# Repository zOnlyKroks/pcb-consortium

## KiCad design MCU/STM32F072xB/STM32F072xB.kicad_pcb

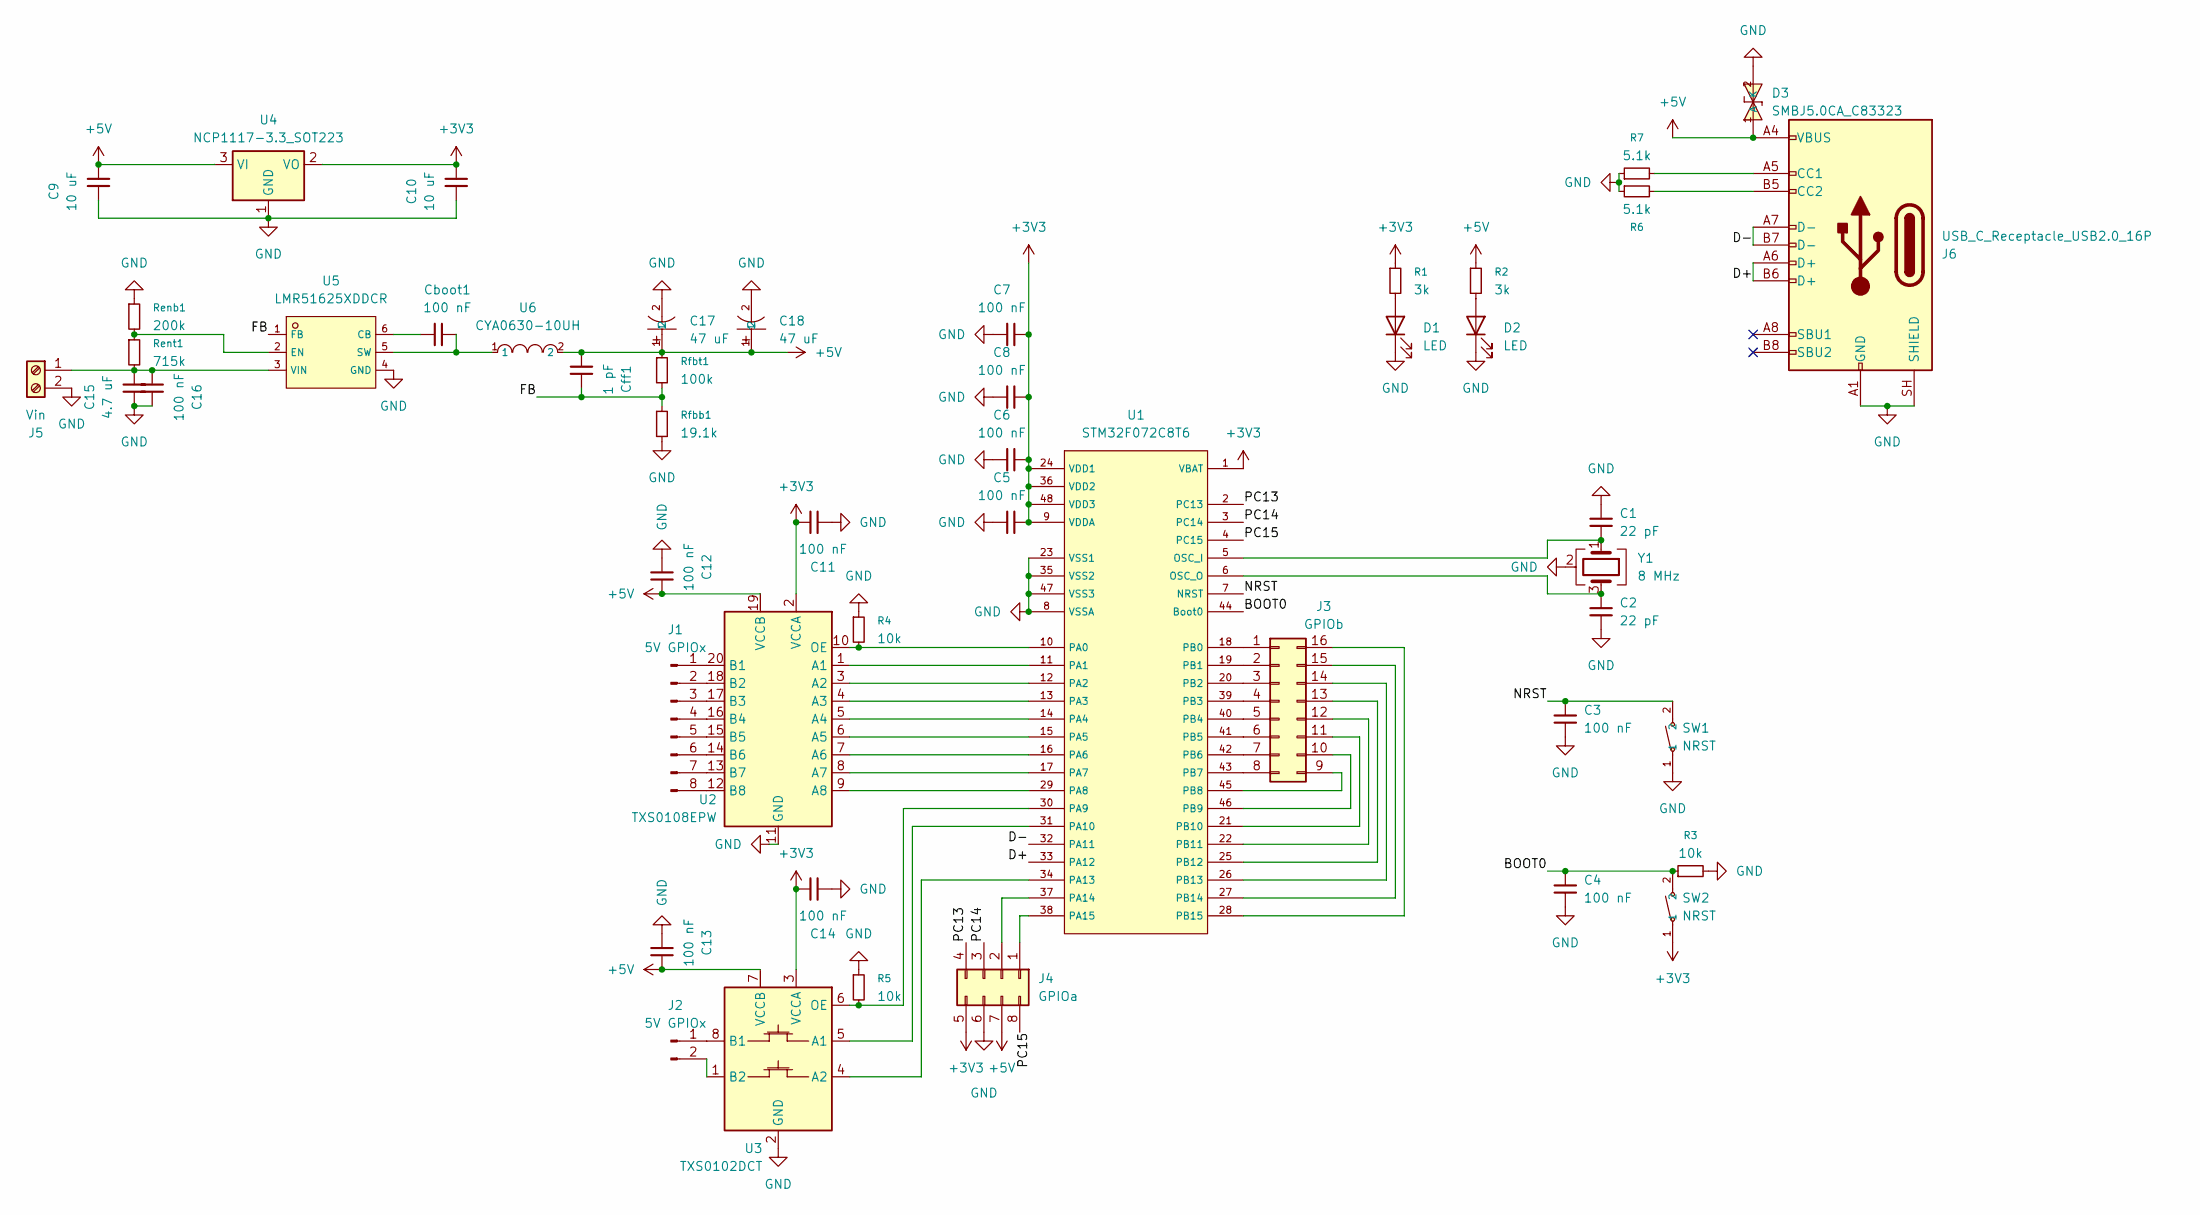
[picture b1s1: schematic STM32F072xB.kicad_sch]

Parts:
C1, C2: 22 pF; C_0603_1608Metric
C3, C4, C5, C6, C7, C8, C11, C12, C13, C14: 100 nF; C_0603_1608Metric
C9, C10: 10 uF; C_0805_2012Metric
C15: 4.7 uF; C_0805_2012Metric
C16: 100 nF; C_0805_2012Metric
C17, C18: 47 uF; C141425_CAP-SMD_BD6_3-L6_6-W6_6-FD; LCSC C141425
Cboot1: 100 nF; C_0805_2012Metric
Cff1: 1 pF; C_0805_2012Metric
D1, D2: LED; LED_0805_2012Metric
D3: SMBJ5.0CA_C83323; C83323_SMB_L4_6-W3_6-LS5_3-BI; LCSC C83323
J1: 5V GPIOx; PinHeader_1x08_P2.54mm_Vertical
J2: 5V GPIOx; PinHeader_1x02_P2.54mm_Vertical
J3: GPIOb; PinHeader_2x08_P2.54mm_Vertical
J4: GPIOa; PinHeader_2x04_P2.54mm_Vertical
J5: Vin; WJ500V-5.08-2P
J6: USB_C_Receptacle_USB2.0_16P; USB_C_Receptacle_HRO_TYPE-C-31-M-12
R1, R2: 3k; R_0603_1608Metric
R3, R4, R5: 10k; R_0603_1608Metric
R6, R7: 5.1k; R_0603_1608Metric
Renb1: 200k; R_0603_1608Metric
Rent1: 715k; R_0603_1608Metric
Rfbb1: 19.1k; R_0603_1608Metric
Rfbt1: 100k; R_0603_1608Metric
SW1, SW2: NRST; C53447012_SW-SMD_L3_9-W3_0-LS5_0; LCSC C53447012
U1: STM32F072C8T6; C80488_LQFP-48_L7_0-W7_0-P0_50-LS9_0-BL; LCSC C80488
U2: TXS0108EPW; TSSOP-20_4.4x6.5mm_P0.65mm
U3: TXS0102DCT; SSOP-8_2.95x2.8mm_P0.65mm
U4: NCP1117-3.3_SOT223; SOT-223-3_TabPin2
U5: LMR51625XDDCR; C44750835_SOT-23-6_L2_9-W1_6-P0_95-LS2_9-BL; LCSC C44750835
U6: CYA0630-10UH; C5189958_IND-SMD_L7_2-W6_6_GPSR07X0; LCSC C5189958
Y1: 8 MHz; Crystal_SMD_3225-4Pin_3.2x2.5mm

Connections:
+3V3: C5.1, C6.1, C7.1, C8.1, C10.1, C11.1, C14.1, J4.5, R1.1, SW2.1, U1.1 (VBAT), U1.9 (VDDA), U1.24 (VDD1), U1.36 (VDD2), U1.48 (VDD3), U2.2 (VCCA), U3.3 (VCCA), U4.2 (VO)
+5V: C9.1, C12.1, C13.1, C17.1, C18.1, Cff1.1, D3.1 (K), J4.7, J6.A4 (VBUS), J6.A9 (VBUS), J6.B4 (VBUS), J6.B9 (VBUS), R2.1, Rfbt1.1, U2.19 (VCCB), U3.7 (VCCB), U4.3 (VI), U6.2
/BOOT0: C4.2, R3.1, SW2.2, U1.44 (Boot0)
/D+: J6.A6 (D+), J6.B6 (D+), U1.33 (PA12)
/D-: J6.A7 (D-), J6.B7 (D-), U1.32 (PA11)
/FB: Cff1.2, Rfbb1.1, Rfbt1.2, U5.1 (FB)
/NRST: C3.2, SW1.2, U1.7 (NRST)
/PC13: J4.4, U1.2 (PC13)
/PC14: J4.3, U1.3 (PC14)
/PC15: J4.8, U1.4 (PC15)
GND: C1.2, C2.1, C3.1, C4.1, C5.2, C6.2, C7.2, C8.2, C9.2, C10.2, C11.2, C12.2, C13.2, C14.2, C15.2, C16.2, C17.2, C18.2, D1.1 (K), D2.1 (K), D3.2 (A), J4.6, J5.2, J6.A1 (GND), J6.A12 (GND), J6.B1 (GND), J6.B12 (GND), J6.SH (SHIELD), R3.2, R4.1, R5.1, R6.1, R7.1, Renb1.1, Rfbb1.2, SW1.1, U1.8 (VSSA), U1.23 (VSS1), U1.35 (VSS2), U1.47 (VSS3), U2.11 (GND), U3.2 (GND), U4.1 (GND), U5.4 (GND), Y1.2 (G), Y1.4 (G)
unnamed: D1.2 (A), R1.2
unnamed: D2.2 (A), R2.2
unnamed: J1.1, U2.20 (B1)
unnamed: J1.2, U2.18 (B2)
unnamed: J1.3, U2.17 (B3)
unnamed: J1.4, U2.16 (B4)
unnamed: J1.5, U2.15 (B5)
unnamed: J1.6, U2.14 (B6)
unnamed: J1.7, U2.13 (B7)
unnamed: J1.8, U2.12 (B8)
unnamed: J2.1, U3.8 (B1)
unnamed: J2.2, U3.1 (B2)
unnamed: J3.1, U1.18 (PB0)
unnamed: J3.2, U1.19 (PB1)
unnamed: J3.3, U1.20 (PB2)
unnamed: J3.4, U1.39 (PB3)
unnamed: J3.5, U1.40 (PB4)
unnamed: J3.6, U1.41 (PB5)
unnamed: J3.7, U1.42 (PB6)
unnamed: J3.8, U1.43 (PB7)
unnamed: J3.9, U1.45 (PB8)
unnamed: J3.10, U1.46 (PB9)
unnamed: J3.11, U1.21 (PB10)
unnamed: J3.12, U1.22 (PB11)
unnamed: J3.13, U1.25 (PB12)
unnamed: J3.14, U1.26 (PB13)
unnamed: J3.15, U1.27 (PB14)
unnamed: J3.16, U1.28 (PB15)
unnamed: J4.1, U1.38 (PA15)
unnamed: J4.2, U1.37 (PA14)
unnamed: C15.1, C16.1, J5.1, Rent1.2, U5.3 (VIN)
unnamed: J6.A5 (CC1), R7.2
unnamed: J6.B5 (CC2), R6.2
unnamed: C1.1, U1.5 (OSC_I), Y1.1
unnamed: C2.2, U1.6 (OSC_O), Y1.3
unnamed: R4.2, U1.10 (PA0), U2.10 (OE)
unnamed: U1.11 (PA1), U2.1 (A1)
unnamed: U1.12 (PA2), U2.3 (A2)
unnamed: U1.13 (PA3), U2.4 (A3)
unnamed: U1.14 (PA4), U2.5 (A4)
unnamed: U1.15 (PA5), U2.6 (A5)
unnamed: U1.16 (PA6), U2.7 (A6)
unnamed: U1.17 (PA7), U2.8 (A7)
unnamed: U1.29 (PA8), U2.9 (A8)
unnamed: R5.2, U1.30 (PA9), U3.6 (OE)
unnamed: U1.31 (PA10), U3.5 (A1)
unnamed: U1.34 (PA13), U3.4 (A2)
unnamed: Cboot1.1, U5.6 (CB)
unnamed: Renb1.2, Rent1.1, U5.2 (EN)
unnamed: Cboot1.2, U5.5 (SW), U6.1

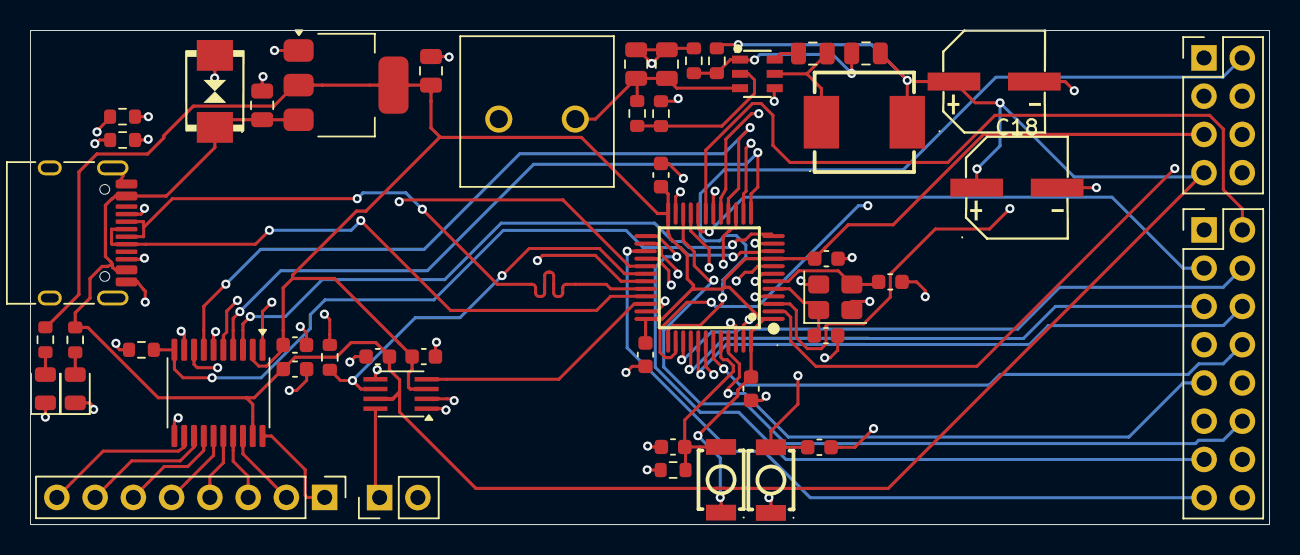
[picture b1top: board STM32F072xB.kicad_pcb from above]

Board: 4 copper layers, 82.3 x 32.8 mm, 49 parts (0 on the bottom side), 61 nets.

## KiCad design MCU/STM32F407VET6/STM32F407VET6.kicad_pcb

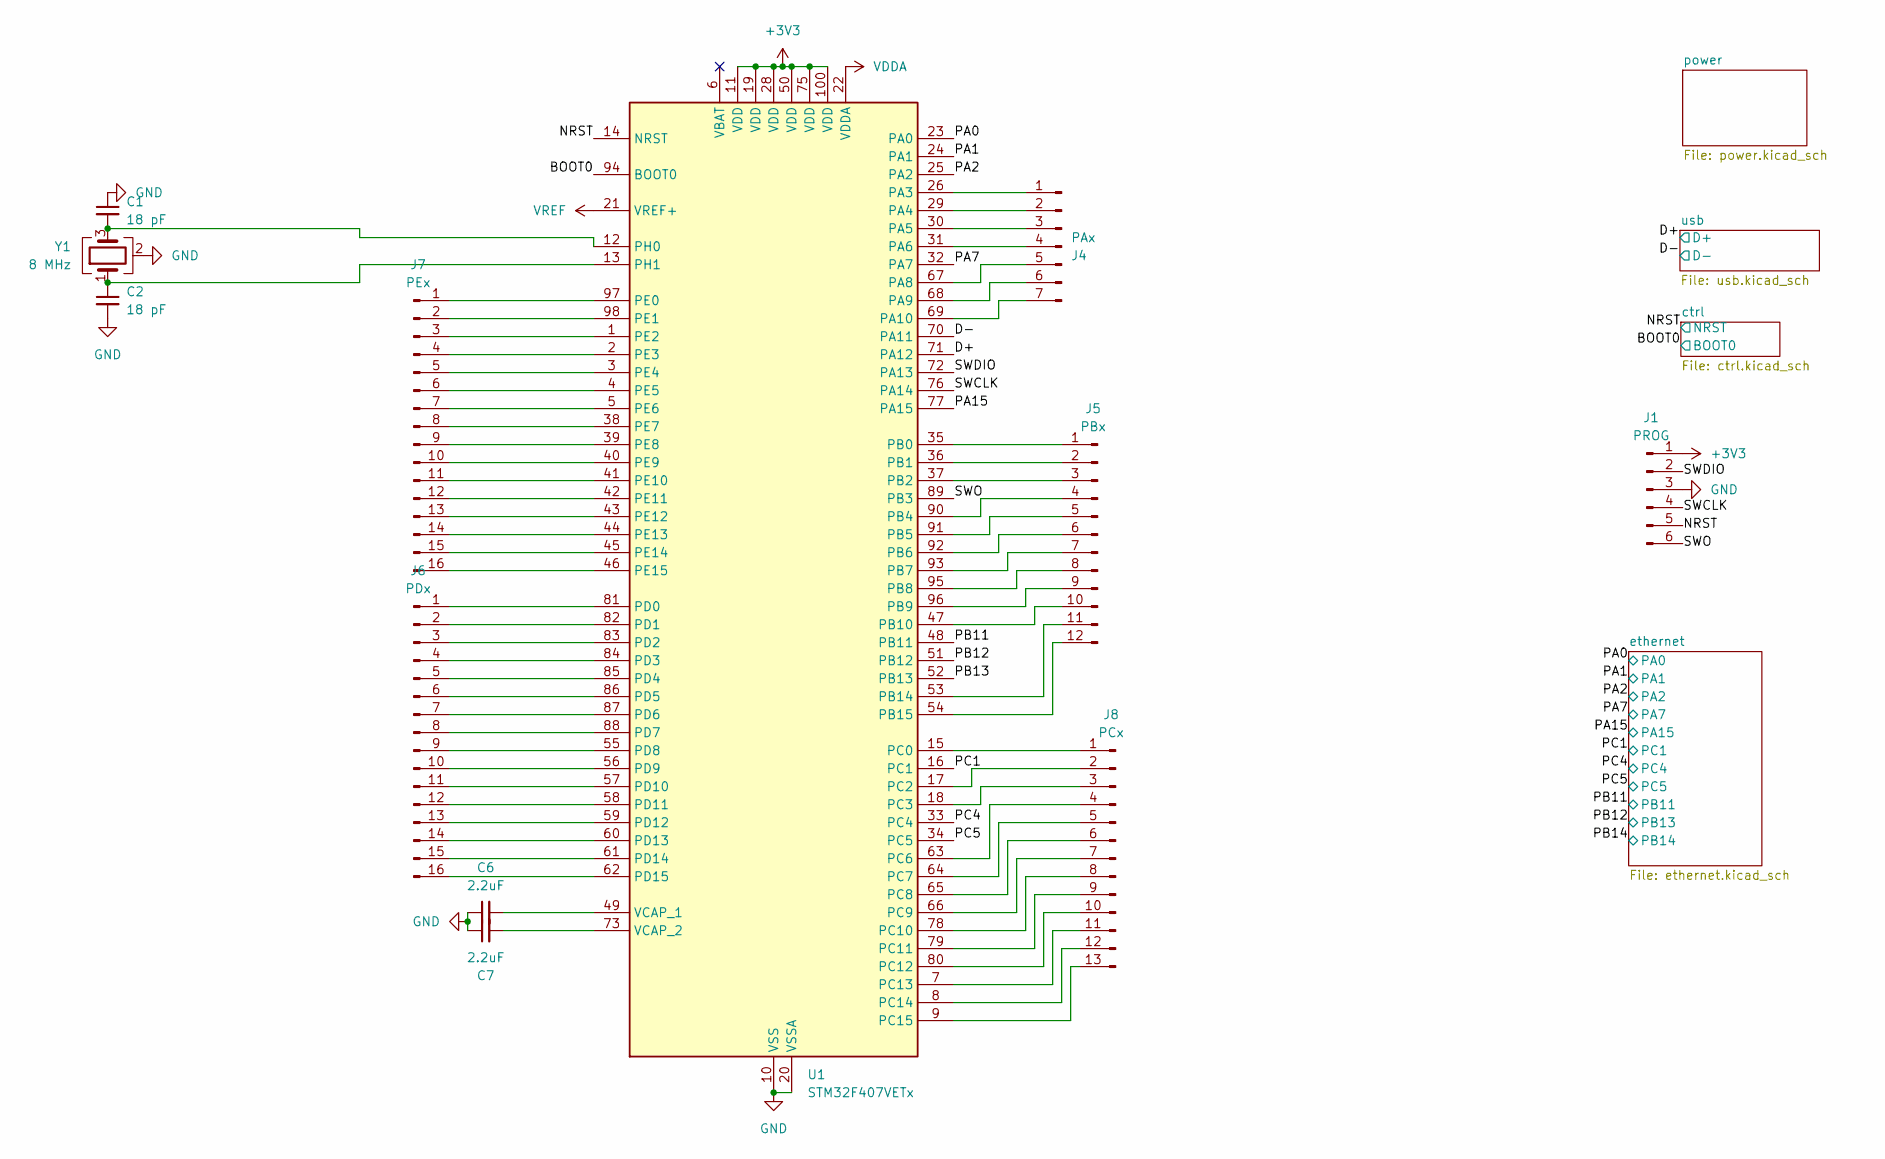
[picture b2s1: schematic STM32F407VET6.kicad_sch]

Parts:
C1, C2: 18 pF; C_0603_1608Metric
C6, C7: 2.2uF; C_0603_1608Metric
J1: PROG; PinHeader_1x06_P2.54mm_Vertical
J4: PAx; PinHeader_1x07_P2.54mm_Vertical
J5: PBx; PinHeader_1x12_P2.54mm_Vertical
J6: PDx; PinHeader_1x16_P2.54mm_Vertical
J7: PEx; PinHeader_1x16_P2.54mm_Vertical
J8: PCx; PinHeader_1x13_P2.54mm_Vertical
U1: STM32F407VETx; LQFP-100_14x14mm_P0.5mm
Y1: 8 MHz; Crystal_SMD_3225-4Pin_3.2x2.5mm

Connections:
+3V3: J1.1, U1.11 (VDD), U1.19 (VDD), U1.28 (VDD), U1.50 (VDD), U1.75 (VDD), U1.100 (VDD); also elsewhere on the board
/BOOT0: U1.94 (BOOT0); also elsewhere on the board
/D+: U1.71 (PA12); also elsewhere on the board
/D-: U1.70 (PA11); also elsewhere on the board
/NRST: J1.5, U1.14 (NRST); also elsewhere on the board
/PA0: U1.23 (PA0); also elsewhere on the board
/PA1: U1.24 (PA1); also elsewhere on the board
/PA2: U1.25 (PA2); also elsewhere on the board
/PA7: U1.32 (PA7); also elsewhere on the board
/PA15: U1.77 (PA15); also elsewhere on the board
/PB11: U1.48 (PB11); also elsewhere on the board
/PB12: U1.51 (PB12); also elsewhere on the board
/PB13: U1.52 (PB13)
/PC1: U1.16 (PC1); also elsewhere on the board
/PC4: U1.33 (PC4); also elsewhere on the board
/PC5: U1.34 (PC5); also elsewhere on the board
/SWCLK: J1.4, U1.76 (PA14)
/SWDIO: J1.2, U1.72 (PA13)
/SWO: J1.6, U1.89 (PB3)
GND: C1.1, C2.2, C6.1, C7.1, J1.3, U1.10 (VSS), U1.20 (VSSA), U1.27 (VSS), U1.74 (VSS), U1.99 (VSS), Y1.2 (G), Y1.4 (G); also elsewhere on the board
unnamed: J4.1, U1.26 (PA3)
unnamed: J4.2, U1.29 (PA4)
unnamed: J4.3, U1.30 (PA5)
unnamed: J4.4, U1.31 (PA6)
unnamed: J4.5, U1.67 (PA8)
unnamed: J4.6, U1.68 (PA9)
unnamed: J4.7, U1.69 (PA10)
unnamed: J5.1, U1.35 (PB0)
unnamed: J5.2, U1.36 (PB1)
unnamed: J5.3, U1.37 (PB2)
unnamed: J5.4, U1.90 (PB4)
unnamed: J5.5, U1.91 (PB5)
unnamed: J5.6, U1.92 (PB6)
unnamed: J5.7, U1.93 (PB7)
unnamed: J5.8, U1.95 (PB8)
unnamed: J5.9, U1.96 (PB9)
unnamed: J5.10, U1.47 (PB10)
unnamed: J5.11, U1.53 (PB14)
unnamed: J5.12, U1.54 (PB15)
unnamed: J6.1, U1.81 (PD0)
unnamed: J6.2, U1.82 (PD1)
unnamed: J6.3, U1.83 (PD2)
unnamed: J6.4, U1.84 (PD3)
unnamed: J6.5, U1.85 (PD4)
unnamed: J6.6, U1.86 (PD5)
unnamed: J6.7, U1.87 (PD6)
unnamed: J6.8, U1.88 (PD7)
unnamed: J6.9, U1.55 (PD8)
unnamed: J6.10, U1.56 (PD9)
unnamed: J6.11, U1.57 (PD10)
unnamed: J6.12, U1.58 (PD11)
unnamed: J6.13, U1.59 (PD12)
unnamed: J6.14, U1.60 (PD13)
unnamed: J6.15, U1.61 (PD14)
unnamed: J6.16, U1.62 (PD15)
unnamed: J7.1, U1.97 (PE0)
unnamed: J7.2, U1.98 (PE1)
unnamed: J7.3, U1.1 (PE2)
unnamed: J7.4, U1.2 (PE3)
unnamed: J7.5, U1.3 (PE4)
unnamed: J7.6, U1.4 (PE5)
unnamed: J7.7, U1.5 (PE6)
unnamed: J7.8, U1.38 (PE7)
unnamed: J7.9, U1.39 (PE8)
unnamed: J7.10, U1.40 (PE9)
unnamed: J7.11, U1.41 (PE10)
unnamed: J7.12, U1.42 (PE11)
unnamed: J7.13, U1.43 (PE12)
unnamed: J7.14, U1.44 (PE13)
unnamed: J7.15, U1.45 (PE14)
unnamed: J7.16, U1.46 (PE15)
unnamed: J8.1, U1.15 (PC0)
unnamed: J8.2, U1.17 (PC2)
unnamed: J8.3, U1.18 (PC3)
unnamed: J8.4, U1.63 (PC6)
unnamed: J8.5, U1.64 (PC7)
unnamed: J8.6, U1.65 (PC8)
unnamed: J8.7, U1.66 (PC9)
unnamed: J8.8, U1.78 (PC10)
unnamed: J8.9, U1.79 (PC11)
unnamed: J8.10, U1.80 (PC12)
unnamed: J8.11, U1.7 (PC13)
unnamed: J8.12, U1.8 (PC14)
unnamed: J8.13, U1.9 (PC15)
unnamed: C1.2, U1.12 (PH0), Y1.3
unnamed: C2.1, U1.13 (PH1), Y1.1
unnamed: C6.2, U1.49 (VCAP_1)
unnamed: C7.2, U1.73 (VCAP_2)
VDDA: U1.22 (VDDA); also elsewhere on the board
VREF: U1.21 (VREF+); also elsewhere on the board

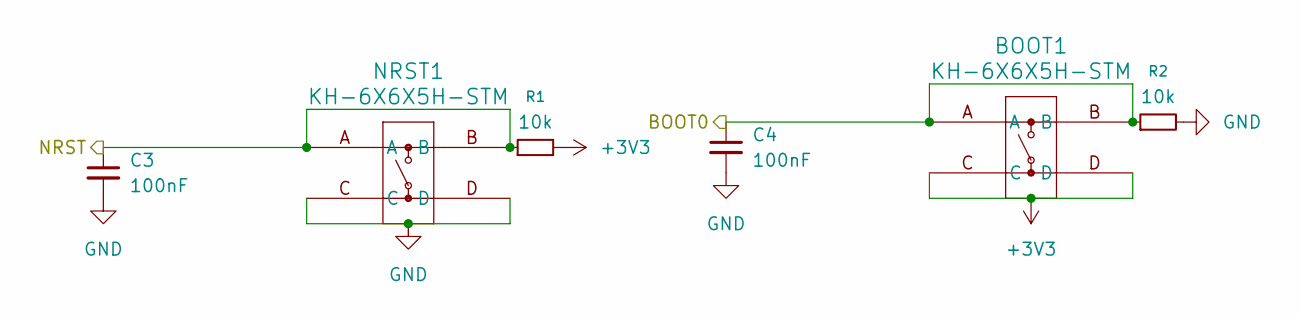
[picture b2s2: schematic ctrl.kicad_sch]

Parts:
BOOT1: KH-6X6X5H-STM; KH-6X6X5H-STM_SKE
C3, C4: 100nF; C_0603_1608Metric
NRST1: KH-6X6X5H-STM; KH-6X6X5H-STM_SKE
R1, R2: 10k; R_0603_1608Metric

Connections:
+3V3: BOOT1.C, BOOT1.D, R1.2; also elsewhere on the board
/BOOT0: BOOT1.A, BOOT1.B, C4.1, R2.1; also elsewhere on the board
/NRST: C3.1, NRST1.A, NRST1.B, R1.1; also elsewhere on the board
GND: C3.2, C4.2, NRST1.C, NRST1.D, R2.2; also elsewhere on the board

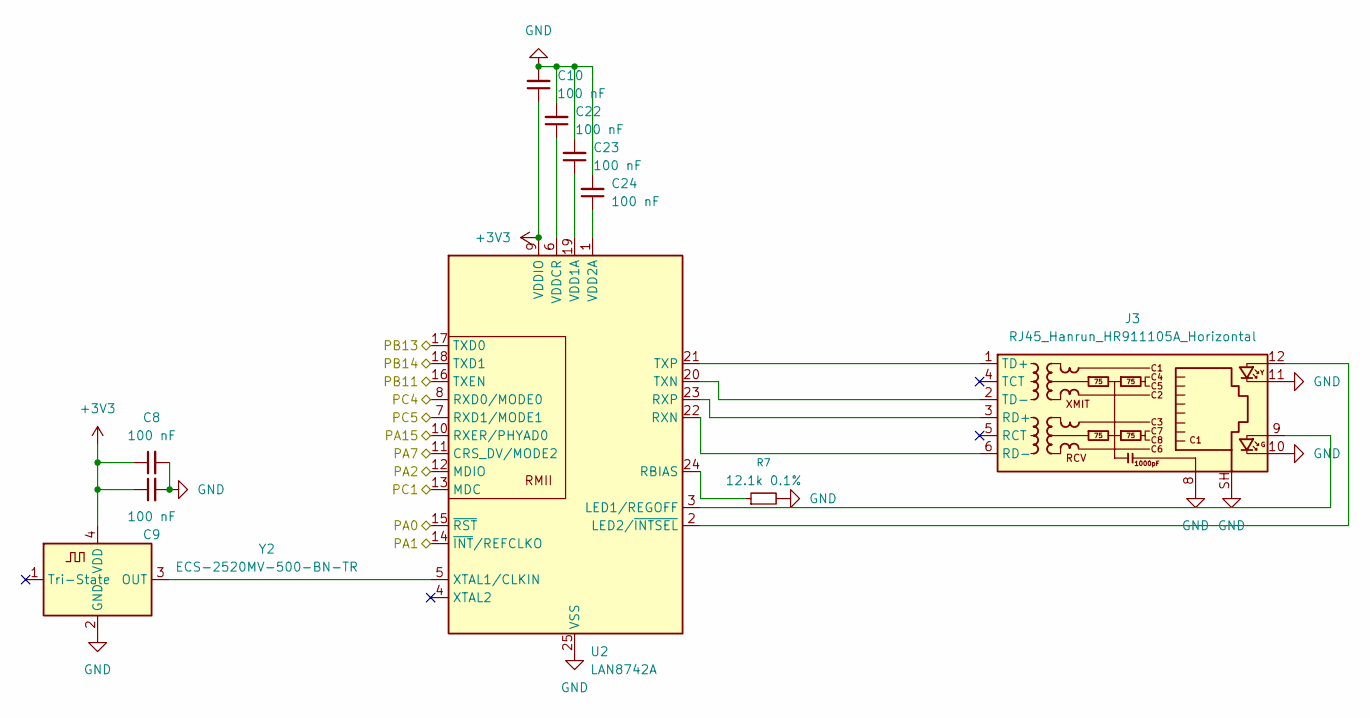
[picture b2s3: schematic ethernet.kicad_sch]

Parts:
C8, C9, C10, C22, C23, C24: 100 nF; C_0603_1608Metric
J3: RJ45_Hanrun_HR911105A_Horizontal
R7: 12.1k 0.1%; R_0603_1608Metric
U2: LAN8742A; VQFN-24-1EP_4x4mm_P0.5mm_EP2.5x2.5mm_ThermalVias
Y2: ECS-2520MV-500-BN-TR; Oscillator_SMD_ECS_2520MV-xxx-xx-4Pin_2.5x2.0mm

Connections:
+3V3: C8.1, C9.1, C10.1, U2.9 (VDDIO), Y2.4 (VDD); also elsewhere on the board
/PA0: U2.15 (~RST); also elsewhere on the board
/PA1: U2.14 (~INT/REFCLKO); also elsewhere on the board
/PA2: U2.12 (MDIO); also elsewhere on the board
/PA7: U2.11 (CRS_DV/MODE2); also elsewhere on the board
/PA15: U2.10 (RXER/PHYAD0); also elsewhere on the board
/PB11: U2.16 (TXEN); also elsewhere on the board
/PB12: U2.17 (TXD0); also elsewhere on the board
/PB14: U2.18 (TXD1)
/PC1: U2.13 (MDC); also elsewhere on the board
/PC4: U2.8 (RXD0/MODE0); also elsewhere on the board
/PC5: U2.7 (RXD1/MODE1); also elsewhere on the board
GND: C8.2, C9.2, C10.2, C22.2, C23.2, C24.2, J3.8, J3.10, J3.11, J3.SH, R7.2, U2.25 (VSS), Y2.2 (GND); also elsewhere on the board
unnamed: J3.3 (RD+), U2.23 (RXP)
unnamed: J3.6 (RD-), U2.22 (RXN)
unnamed: J3.1 (TD+), U2.21 (TXP)
unnamed: J3.2 (TD-), U2.20 (TXN)
unnamed: J3.9, U2.3 (LED1/REGOFF)
unnamed: J3.12, U2.2 (LED2/~INTSEL)
unnamed: R7.1, U2.24 (RBIAS)
unnamed: C23.1, U2.19 (VDD1A)
unnamed: C24.1, U2.1 (VDD2A)
unnamed: C22.1, U2.6 (VDDCR)
unnamed: U2.5 (XTAL1/CLKIN), Y2.3 (OUT)

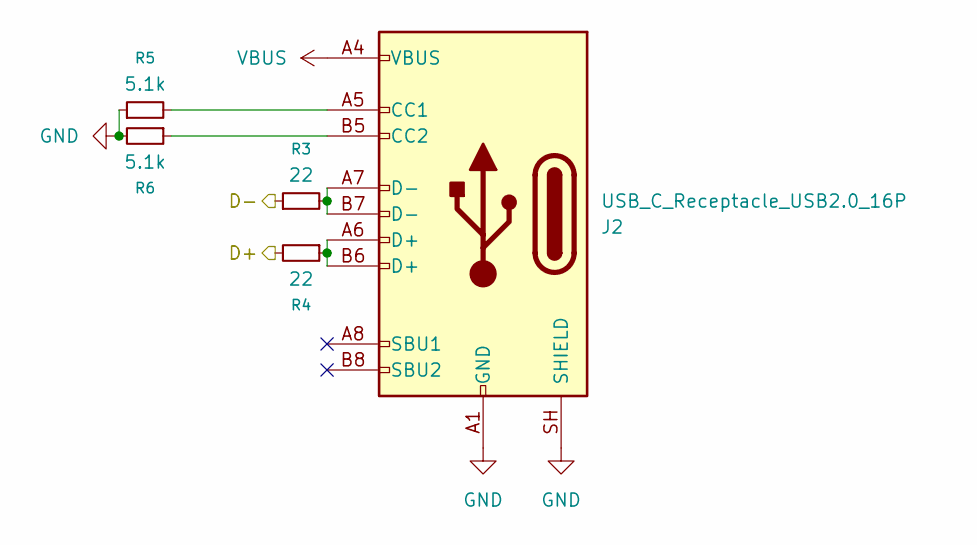
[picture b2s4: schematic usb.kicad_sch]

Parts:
J2: USB_C_Receptacle_USB2.0_16P; USB_C_Receptacle_HRO_TYPE-C-31-M-12
R3, R4: 22; R_0603_1608Metric
R5, R6: 5.1k; R_0603_1608Metric

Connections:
/D+: R4.2; also elsewhere on the board
/D-: R3.1; also elsewhere on the board
GND: J2.A1 (GND), J2.A12 (GND), J2.B1 (GND), J2.B12 (GND), J2.SH (SHIELD), R5.1, R6.2; also elsewhere on the board
unnamed: J2.A5 (CC1), R5.2
unnamed: J2.B5 (CC2), R6.1
unnamed: J2.A6 (D+), J2.B6 (D+), R4.1
unnamed: J2.A7 (D-), J2.B7 (D-), R3.2
VBUS: J2.A4 (VBUS), J2.A9 (VBUS), J2.B4 (VBUS), J2.B9 (VBUS); also elsewhere on the board

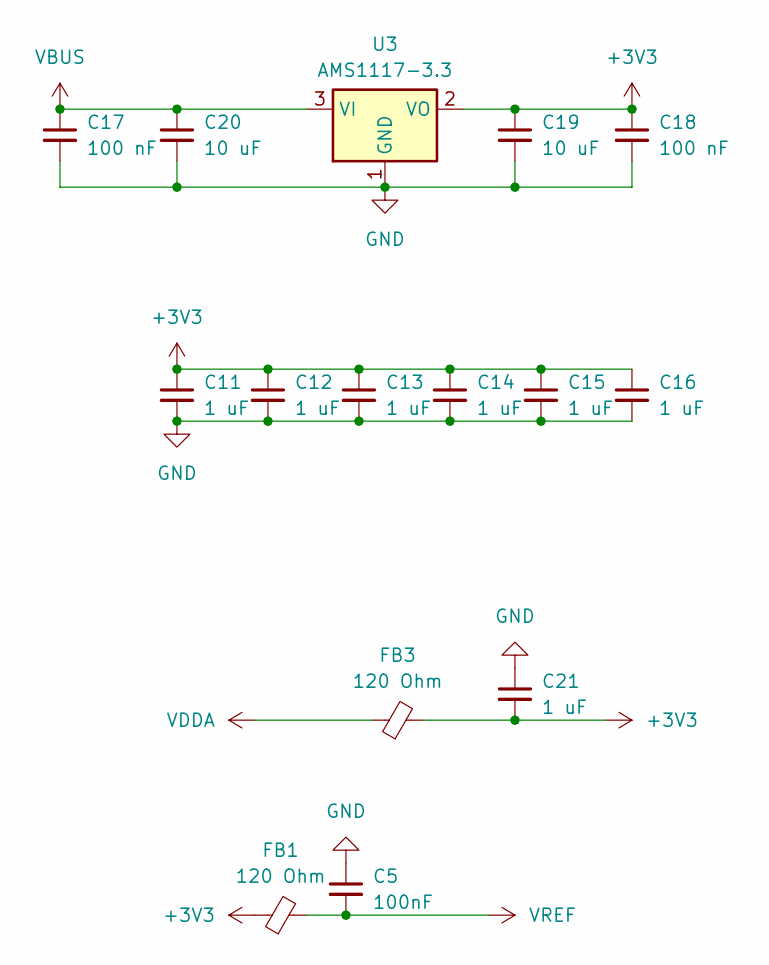
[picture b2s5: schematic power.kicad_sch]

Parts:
C5: 100nF; C_0603_1608Metric
C11, C12, C13, C14, C15, C16, C21: 1 uF; C_0603_1608Metric
C17, C18: 100 nF; C_0603_1608Metric
C19, C20: 10 uF; C_0603_1608Metric
FB1, FB3: 120 Ohm; R_0603_1608Metric
U3: AMS1117-3.3; SOT-223-3_TabPin2

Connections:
+3V3: C11.1, C12.1, C13.1, C14.1, C15.1, C16.1, C18.1, C19.1, C21.2, FB1.1, FB3.2, U3.2 (VO); also elsewhere on the board
GND: C5.1, C11.2, C12.2, C13.2, C14.2, C15.2, C16.2, C17.2, C18.2, C19.2, C20.2, C21.1, U3.1 (GND); also elsewhere on the board
VBUS: C17.1, C20.1, U3.3 (VI); also elsewhere on the board
VDDA: FB3.1; also elsewhere on the board
VREF: C5.2, FB1.2; also elsewhere on the board

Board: 4 copper layers, 48 parts (0 on the bottom side), 105 nets, no tracks yet.

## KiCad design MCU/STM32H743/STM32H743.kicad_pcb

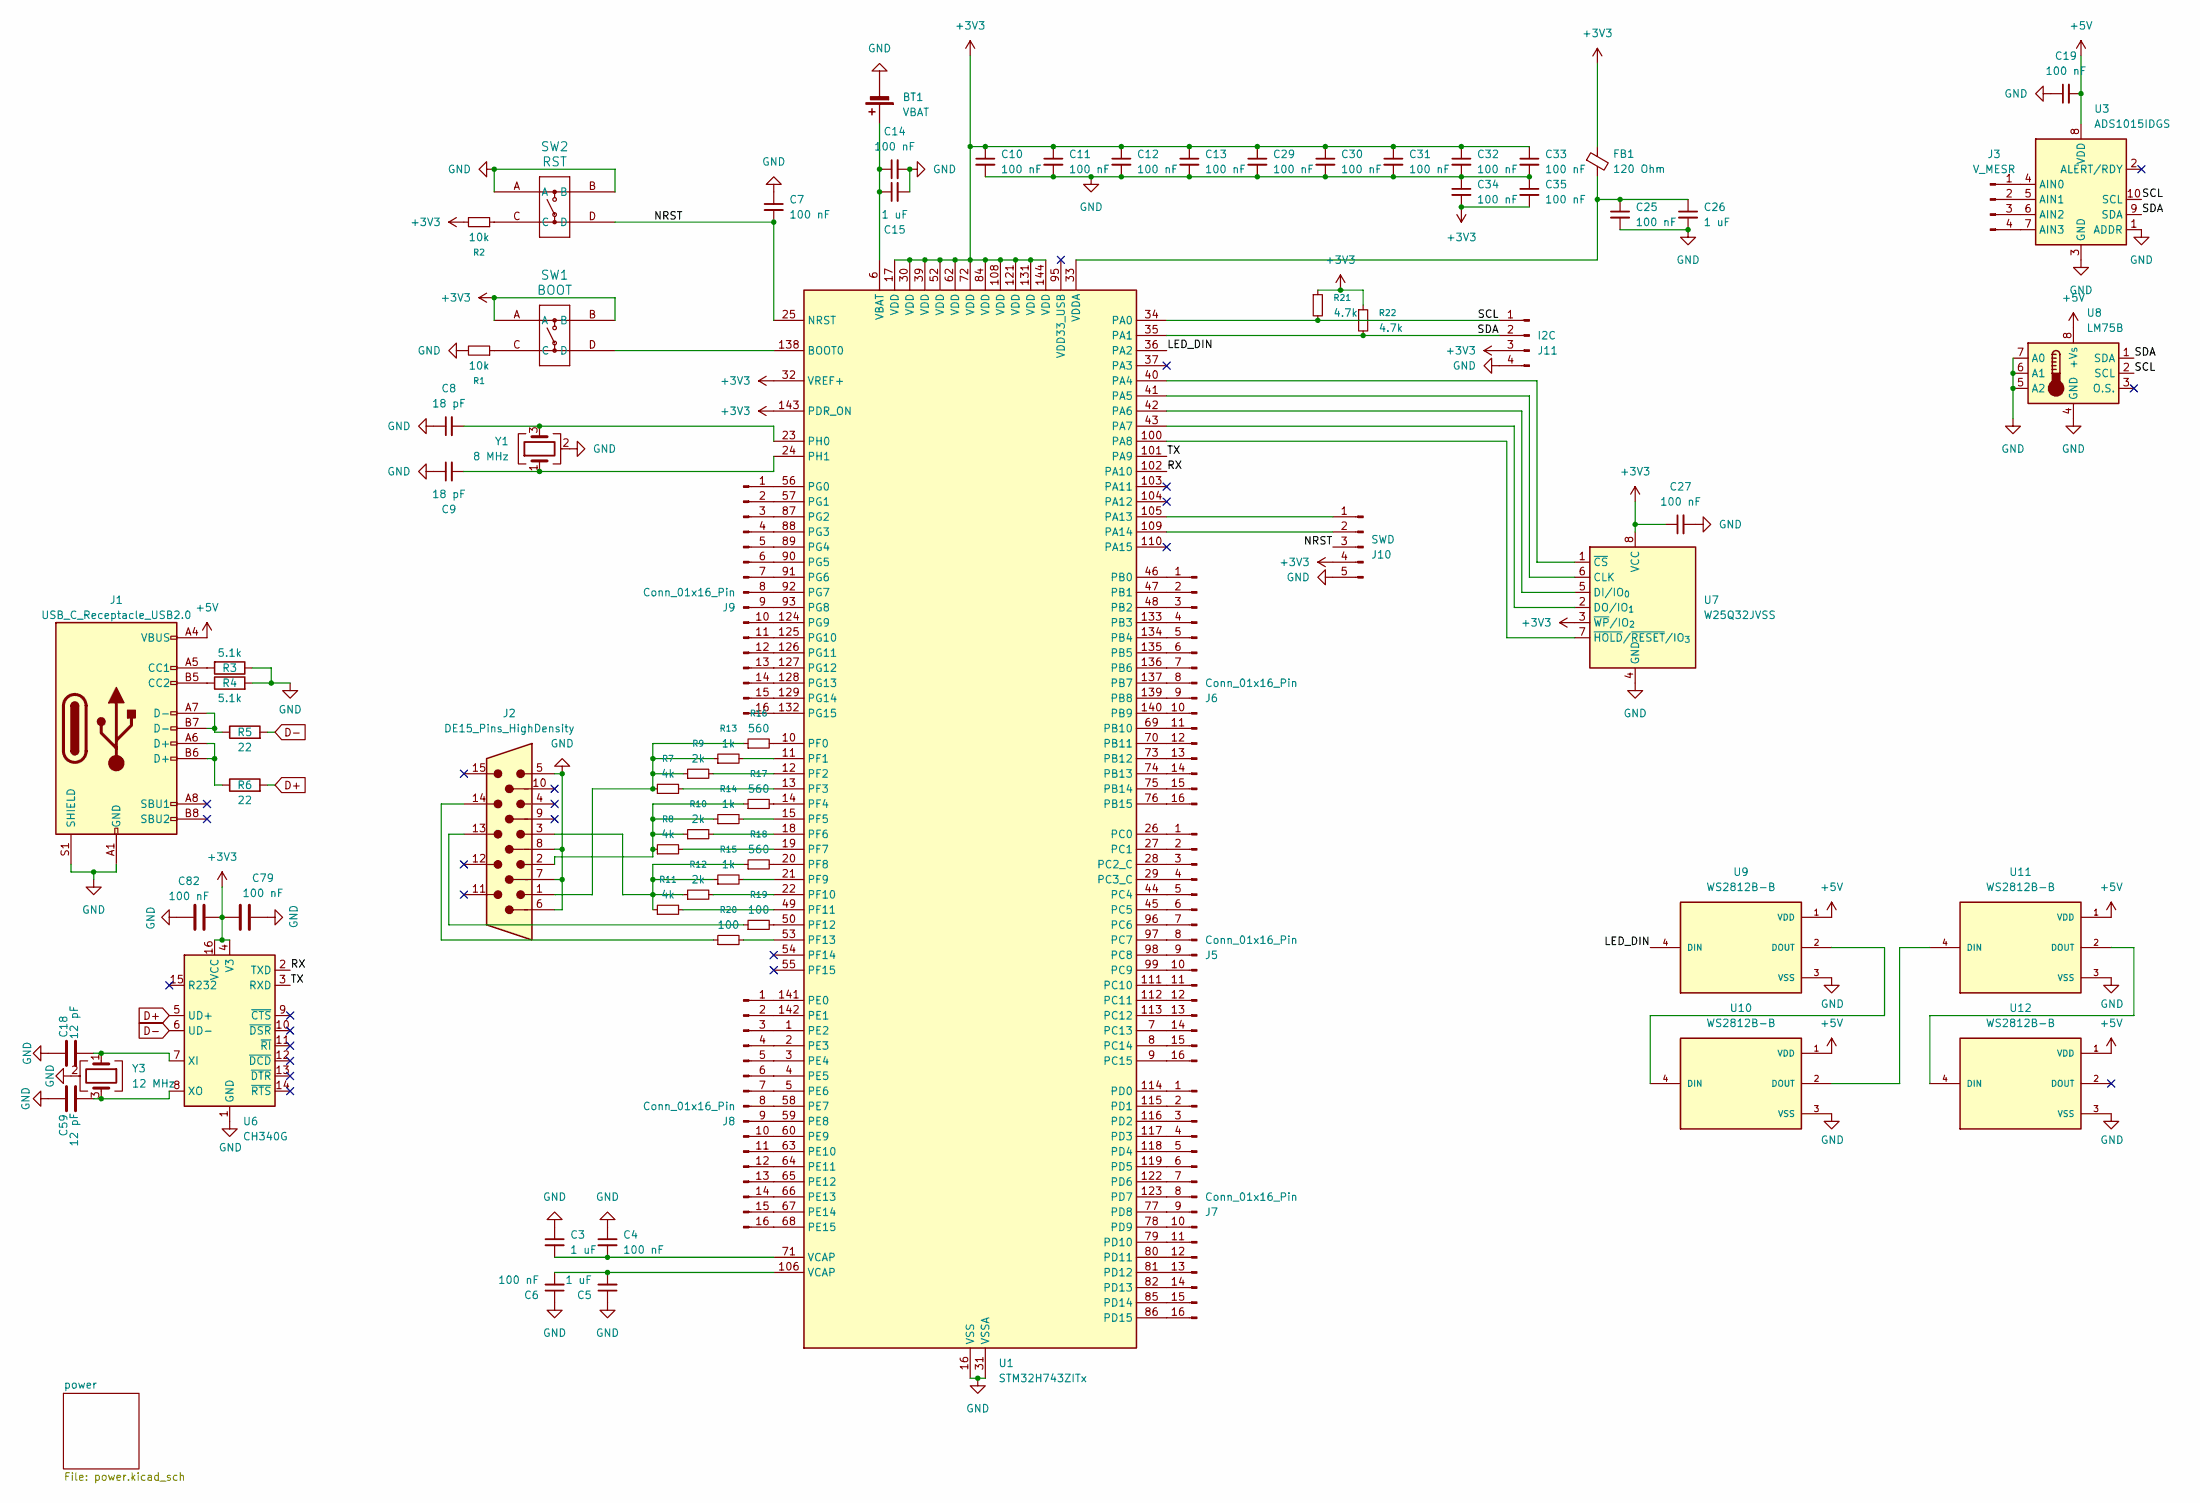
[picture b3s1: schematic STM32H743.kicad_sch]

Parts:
BT1: VBAT; BatteryHolder_Keystone_103_1x20mm
C3, C5, C15, C26: 1 uF; C_0402_1005Metric
C4, C6, C7, C10, C11, C12, C13, C14, C19, C25, C27, C29, C30, C31, C32, C33, C34, C35: 100 nF; C_0402_1005Metric
C8, C9: 18 pF; C_0402_1005Metric
C18: 12 pF; C_0402_1005Metric; LCSC Part # C107108
C59: 12 pF; C_0805_2012Metric; LCSC Part # C107108
C79, C82: 100 nF; C_0805_2012Metric; LCSC Part # C49678
FB1: 120 Ohm; R_0603_1608Metric
J1: USB_C_Receptacle_USB2.0; USB_C_Receptacle_HRO_TYPE-C-31-M-12; JlcRotOffset 180
J2: DE15_Pins_HighDensity; DSUB-15-HD_Pins_Horizontal_P2.29x1.90mm_EdgePinOffset3.03mm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
J3: V_MESR; PinHeader_1x04_P2.54mm_Vertical
J5, J6, J7, J8, J9: Conn_01x16_Pin; PinHeader_1x16_P2.54mm_Vertical
J10: SWD; PinHeader_1x05_P2.54mm_Vertical
J11: I2C
R1, R2: 10k; R_0402_1005Metric
R3, R4: 5.1k; R_0805_2012Metric; LCSC Part # C27834
R5, R6: 22; R_0805_2012Metric; LCSC Part # C17561
R7, R8, R11: 4k; R_0603_1608Metric
R9, R10, R12: 2k; R_0603_1608Metric
R13, R14, R15: 1k; R_0603_1608Metric
R16, R17, R18: 560; R_0603_1608Metric
R19, R20: 100; R_0603_1608Metric
R21, R22: 4.7k; R_0402_1005Metric
SW1: BOOT; KH-6X6X5H-STM_SKE
SW2: RST; KH-6X6X5H-STM_SKE
U1: STM32H743ZITx; LQFP-144_20x20mm_P0.5mm
U3: ADS1015IDGS; TSSOP-10_3x3mm_P0.5mm
U6: CH340G; SOIC-16_3.9x9.9mm_P1.27mm
U7: W25Q32JVSS; SOIC-8_5.3x5.3mm_P1.27mm
U8: LM75B; SOIC-8_3.9x4.9mm_P1.27mm
U9, U10, U11, U12: WS2812B-B; LED_WS2812B-B; PARTREV 5; LCSC Part # C2761795
Y1: 8 MHz; Crystal_SMD_3225-4Pin_3.2x2.5mm
Y3: 12 MHz; Crystal_SMD_3225-4Pin_3.2x2.5mm; LCSC Part # C19631429

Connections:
+3V3: C10.1, C11.1, C12.1, C13.1, C27.1, C29.1, C30.1, C31.1, C32.1, C33.1, C34.2, C35.2, C79.2, C82.1, FB1.1, J10.4, J11.3, R2.2, R21.1, R22.1, SW1.A, SW1.B, U1.17 (VDD), U1.30 (VDD), U1.32 (VREF+), U1.39 (VDD), U1.52 (VDD), U1.62 (VDD), U1.72 (VDD), U1.84 (VDD), U1.108 (VDD), U1.121 (VDD), U1.131 (VDD), U1.143 (PDR_ON), U1.144 (VDD), U6.4 (V3), U6.16 (VCC), U7.3 (~WP/IO_{2}), U7.8 (VCC); also elsewhere on the board
+5V: C19.2, J1.A4 (VBUS), J1.A9 (VBUS), J1.B4 (VBUS), J1.B9 (VBUS), U3.8 (VDD), U8.8 (+Vs), U9.1 (VDD), U10.1 (VDD), U11.1 (VDD), U12.1 (VDD); also elsewhere on the board
/LED_DIN: U1.36 (PA2), U9.4 (DIN)
/NRST: C7.2, J10.3, SW2.D, U1.25 (NRST)
/RX: U1.102 (PA10), U6.2 (TXD)
/SCL: J11.1, R21.2, U1.34 (PA0), U3.10 (SCL), U8.2 (SCL)
/SDA: J11.2, R22.2, U1.35 (PA1), U3.9 (SDA), U8.1 (SDA)
/TX: U1.101 (PA9), U6.3 (RXD)
D+: R6.2, U6.5 (UD+)
D-: R5.2, U6.6 (UD-)
GND: BT1.2 (-), C3.1, C4.1, C5.1, C6.1, C7.1, C8.1, C9.1, C10.2, C11.2, C12.2, C13.2, C14.2, C15.2, C18.1, C19.1, C25.2, C26.2, C27.2, C29.2, C30.2, C31.2, C32.2, C33.2, C34.1, C35.1, C59.1, C79.1, C82.2, J1.A1 (GND), J1.A12 (GND), J1.B1 (GND), J1.B12 (GND), J1.S1 (SHIELD), J2.5, J2.6, J2.7, J2.8, J10.5, J11.4, R1.2, R3.1, R4.2, SW2.A, SW2.B, U1.16 (VSS), U1.31 (VSSA), U1.38 (VSS), U1.51 (VSS), U1.61 (VSS), U1.83 (VSS), U1.94 (VSS), U1.107 (VSS), U1.120 (VSS), U1.130 (VSS), U3.1 (ADDR), U3.3 (GND), U6.1 (GND), U7.4 (GND), U8.4 (GND), U8.5 (A2), U8.6 (A1), U8.7 (A0), U9.3 (VSS), U10.3 (VSS), U11.3 (VSS), U12.3 (VSS), Y1.2 (G), Y1.4 (G), Y3.2 (G), Y3.4 (G); also elsewhere on the board
unnamed: BT1.1 (+), C14.1, C15.1, U1.6 (VBAT)
unnamed: C3.2, C4.2, U1.71 (VCAP)
unnamed: C5.2, C6.2, U1.106 (VCAP)
unnamed: J1.A5 (CC1), R3.2
unnamed: J1.B5 (CC2), R4.1
unnamed: J1.A6 (D+), J1.B6 (D+), R6.1
unnamed: J1.A7 (D-), J1.B7 (D-), R5.1
unnamed: J2.1, R7.1, R9.1, R13.1, R16.1
unnamed: J2.2, R8.1, R10.1, R14.1, R17.1
unnamed: J2.3, R11.1, R12.1, R15.1, R18.1
unnamed: J2.13, R19.1
unnamed: J2.14, R20.1
unnamed: J3.1, U3.4 (AIN0)
unnamed: J3.2, U3.5 (AIN1)
unnamed: J3.3, U3.6 (AIN2)
unnamed: J3.4, U3.7 (AIN3)
unnamed: J5.1, U1.26 (PC0)
unnamed: J5.2, U1.27 (PC1)
unnamed: J5.3, U1.28 (PC2_C)
unnamed: J5.4, U1.29 (PC3_C)
unnamed: J5.5, U1.44 (PC4)
unnamed: J5.6, U1.45 (PC5)
unnamed: J5.7, U1.96 (PC6)
unnamed: J5.8, U1.97 (PC7)
unnamed: J5.9, U1.98 (PC8)
unnamed: J5.10, U1.99 (PC9)
unnamed: J5.11, U1.111 (PC10)
unnamed: J5.12, U1.112 (PC11)
unnamed: J5.13, U1.113 (PC12)
unnamed: J5.14, U1.7 (PC13)
unnamed: J5.15, U1.8 (PC14)
unnamed: J5.16, U1.9 (PC15)
unnamed: J6.1, U1.46 (PB0)
unnamed: J6.2, U1.47 (PB1)
unnamed: J6.3, U1.48 (PB2)
unnamed: J6.4, U1.133 (PB3)
unnamed: J6.5, U1.134 (PB4)
unnamed: J6.6, U1.135 (PB5)
unnamed: J6.7, U1.136 (PB6)
unnamed: J6.8, U1.137 (PB7)
unnamed: J6.9, U1.139 (PB8)
unnamed: J6.10, U1.140 (PB9)
unnamed: J6.11, U1.69 (PB10)
unnamed: J6.12, U1.70 (PB11)
unnamed: J6.13, U1.73 (PB12)
unnamed: J6.14, U1.74 (PB13)
unnamed: J6.15, U1.75 (PB14)
unnamed: J6.16, U1.76 (PB15)
unnamed: J7.1, U1.114 (PD0)
unnamed: J7.2, U1.115 (PD1)
unnamed: J7.3, U1.116 (PD2)
unnamed: J7.4, U1.117 (PD3)
unnamed: J7.5, U1.118 (PD4)
unnamed: J7.6, U1.119 (PD5)
unnamed: J7.7, U1.122 (PD6)
unnamed: J7.8, U1.123 (PD7)
unnamed: J7.9, U1.77 (PD8)
unnamed: J7.10, U1.78 (PD9)
unnamed: J7.11, U1.79 (PD10)
unnamed: J7.12, U1.80 (PD11)
unnamed: J7.13, U1.81 (PD12)
unnamed: J7.14, U1.82 (PD13)
unnamed: J7.15, U1.85 (PD14)
unnamed: J7.16, U1.86 (PD15)
unnamed: J8.1, U1.141 (PE0)
unnamed: J8.2, U1.142 (PE1)
unnamed: J8.3, U1.1 (PE2)
unnamed: J8.4, U1.2 (PE3)
unnamed: J8.5, U1.3 (PE4)
unnamed: J8.6, U1.4 (PE5)
unnamed: J8.7, U1.5 (PE6)
unnamed: J8.8, U1.58 (PE7)
unnamed: J8.9, U1.59 (PE8)
unnamed: J8.10, U1.60 (PE9)
unnamed: J8.11, U1.63 (PE10)
unnamed: J8.12, U1.64 (PE11)
unnamed: J8.13, U1.65 (PE12)
unnamed: J8.14, U1.66 (PE13)
unnamed: J8.15, U1.67 (PE14)
unnamed: J8.16, U1.68 (PE15)
unnamed: J9.1, U1.56 (PG0)
unnamed: J9.2, U1.57 (PG1)
unnamed: J9.3, U1.87 (PG2)
unnamed: J9.4, U1.88 (PG3)
unnamed: J9.5, U1.89 (PG4)
unnamed: J9.6, U1.90 (PG5)
unnamed: J9.7, U1.91 (PG6)
unnamed: J9.8, U1.92 (PG7)
unnamed: J9.9, U1.93 (PG8)
unnamed: J9.10, U1.124 (PG9)
unnamed: J9.11, U1.125 (PG10)
unnamed: J9.12, U1.126 (PG11)
unnamed: J9.13, U1.127 (PG12)
unnamed: J9.14, U1.128 (PG13)
unnamed: J9.15, U1.129 (PG14)
unnamed: J9.16, U1.132 (PG15)
unnamed: J10.1, U1.105 (PA13)
unnamed: J10.2, U1.109 (PA14)
unnamed: R1.1, SW1.C
unnamed: R2.1, SW2.C
unnamed: SW1.D, U1.138 (BOOT0)
unnamed: U1.40 (PA4), U7.1 (~CS)
unnamed: U1.41 (PA5), U7.6 (CLK)
unnamed: U1.42 (PA6), U7.5 (DI/IO_{0})
unnamed: U1.43 (PA7), U7.2 (DO/IO_{1})
unnamed: U1.100 (PA8), U7.7 (~HOLD/~RESET/IO_{3})
unnamed: R16.2, U1.10 (PF0)
unnamed: R13.2, U1.11 (PF1)
unnamed: R9.2, U1.12 (PF2)
unnamed: R7.2, U1.13 (PF3)
unnamed: R17.2, U1.14 (PF4)
unnamed: R14.2, U1.15 (PF5)
unnamed: R10.2, U1.18 (PF6)
unnamed: R8.2, U1.19 (PF7)
unnamed: R18.2, U1.20 (PF8)
unnamed: R15.2, U1.21 (PF9)
unnamed: R12.2, U1.22 (PF10)
unnamed: R11.2, U1.49 (PF11)
unnamed: R19.2, U1.50 (PF12)
unnamed: R20.2, U1.53 (PF13)
unnamed: C8.2, U1.23 (PH0), Y1.3
unnamed: C9.2, U1.24 (PH1), Y1.1
unnamed: C25.1, C26.1, FB1.2, U1.33 (VDDA)
unnamed: C18.2, U6.7 (XI), Y3.1
unnamed: C59.2, U6.8 (XO), Y3.3
unnamed: U9.2 (DOUT), U10.4 (DIN)
unnamed: U10.2 (DOUT), U11.4 (DIN)
unnamed: U11.2 (DOUT), U12.4 (DIN)
